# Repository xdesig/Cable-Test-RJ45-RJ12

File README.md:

# Cable Test V0.4

You want a PCB to exercise or learn to solder THT components, here you have one of many.
This provides you with a device to test network cables (RJ45) and telephone cables (RJ12 / 11),
made with normal components, (the most complicated being the LED bar).
You can be complemented with more diodes 1N4148 in anti-parallel soldiers under the LEDS (2, 5..9) to allow to check all cable faults.

Buy PCB in [PCBWAY]

![Top view][DEM]
![Render][PHT]
![Botom view][RENDER]

#B.O.M.
<table cellspacing="0" border="0">
	<colgroup width="38"></colgroup>
	<colgroup width="70"></colgroup>
	<colgroup span="2" width="133"></colgroup>
	<colgroup width="122"></colgroup>
	<colgroup width="85"></colgroup>
	<tr>
		<td height="17" align="left">Qty </td>
		<td align="left">Value</td>
		<td align="left">Device</td>
		<td align="left">Package</td>
		<td align="left">Parts</td>
		<td align="left">Description</td>
	</tr>
	<tr>
		<td height="17" align="left"><br></td>
		<td align="left"><br></td>
		<td align="left"><br></td>
		<td align="left"><br></td>
		<td align="left"><br></td>
		<td align="left"><br></td>
	</tr>
	<tr>
		<td height="17" align="right" sdval="2" sdnum="1110;">2</td>
		<td align="left"><br></td>
		<td align="left"> DS1128-S80BP</td>
		<td align="left">DS1128-S80BP</td>
		<td align="left">J1, J3</td>
		<td align="left">Ethernet Connector</td>
	</tr>
	<tr>
		<td height="17" align="right" sdval="1" sdnum="1110;">1</td>
		<td align="left"><br></td>
		<td align="left"> BATTERY9V</td>
		<td align="left">BATTCON_9V</td>
		<td align="left">BAT1</td>
		<td align="left">Battery Holders</td>
	</tr>
	<tr>
		<td height="17" align="right" sdval="1" sdnum="1110;">2</td>
		<td align="left">100nF</td>
		<td align="left"> C2.5/2</td>
		<td align="left">C2.5-2</td>
		<td align="left">C2, C3</td>
		<td align="left">CAPACITOR</td>
	</tr>
	<tr>
		<td height="17" align="right" sdval="2" sdnum="1110;">2</td>
		<td align="left">10K</td>
		<td align="left"> 1/4 Watt</td>
		<td align="left">0204/7</td>
		<td align="left">R1, R3</td>
		<td align="left">RESISTOR</td>
	</tr>
	<tr>
		<td height="17" align="right" sdval="1" sdnum="1110;">1</td>
		<td align="left">10uF/16V</td>
		<td align="left">2.5mm&ndash;6mm</td>
		<td align="left">E2,5-6</td>
		<td align="left">C1</td>
		<td align="left">POLARIZED CAPACITOR</td>
	</tr>
	<tr>
		<td height="17" align="right" sdval="1" sdnum="1110;">1</td>
		<td align="left">1K</td>
		<td align="left"> R-EU_0204/7</td>
		<td align="left">0204/7</td>
		<td align="left">R4</td>
		<td align="left">RESISTOR</td>
	</tr>
	<tr>
		<td height="17" align="right" sdval="1" sdnum="1110;">8</td>
		<td align="left">1N4148</td>
		<td align="left"> DIODE-D-2.5</td>
		<td align="left">D-2.5</td>
		<td align="left">D1...D8</td>
		<td align="left">DIODE</td>
	</tr>
	<tr>
		<td height="17" align="right" sdval="1" sdnum="1110;">1</td>
		<td align="left">4017N</td>
		<td align="left"> 4017N</td>
		<td align="left">DIL16</td>
		<td align="left">IC2</td>
		<td align="left">COUNTER/DIVIDER</td>
	</tr>
	<tr>
		<td height="17" align="right" sdval="1" sdnum="1110;">1</td>
		<td align="left">47K</td>
		<td align="left"> TRIM_EU-CA6V</td>
		<td align="left">CA6V</td>
		<td align="left">R2</td>
		<td align="left">POTENTIOMETER</td>
	</tr>
	<tr>
		<td height="17" align="right" sdval="1" sdnum="1110;">1</td>
		<td align="left">NE555</td>
		<td align="left"> ICM555</td>
		<td align="left">DIL08</td>
		<td align="left">IC1</td>
		<td align="left">TIMER</td>
	</tr>
	<tr>
		<td height="17" align="right" sdval="1" sdnum="1110;">2</td>
		<td align="left">LB10</td>
		<td align="left"> LB10</td>
		<td align="left">LB10</td>
		<td align="left">LB1,LB2</td>
		<td align="left">10 LED BLOCK</td>
	</tr>
	<tr>
		<td height="17" align="right" sdval="1" sdnum="1110;">1</td>
		<td align="left">SW</td>
		<td align="left"> PB7-0</td>
		<td align="left">PB07_0</td>
		<td align="left">SW1</td>
		<td align="left">8x8mm   DPDT Self-locking Switch</td>
	</tr>
	<tr>
		<td height="17" align="right" sdval="2" sdnum="1110;">2</td>
		<td align="left">RJ11</td>
		<td align="left"> RJ11-6PTH</td>
		<td align="left">95001-6P6C</td>
		<td align="left">J2, J4</td>
		<td align="left">RJ12 Socket 95001-6P6C Female</td>
	</tr>
</table>

## Author and license
* Author: [XDeSIG][TWI01]
* License: CERN-OHL-W V2 [CERN-OHL] and Attribution-ShareAlike 4.0 International [CCBY-SA4.0]

<!-- links -->

[CERN-OHL]: https://ohwr.org/cernohl
[CCBY-SA4.0]: http://creativecommons.org/licenses/by-sa/4.0/
[TWI01]: https://twitter.com/xdesig
[DEM]: Cable-Test-RJ45-RJ12_DEM.png
[PHT]: Cable-Test-RJ45-RJ12_MASTER.png
[RENDER]: Cable-Test-RJ45-RJ12_REMOTE.png

[PCBWAY]: https://www.pcbway.com/project/shareproject/Cable_Test_RJ45___RJ12.html

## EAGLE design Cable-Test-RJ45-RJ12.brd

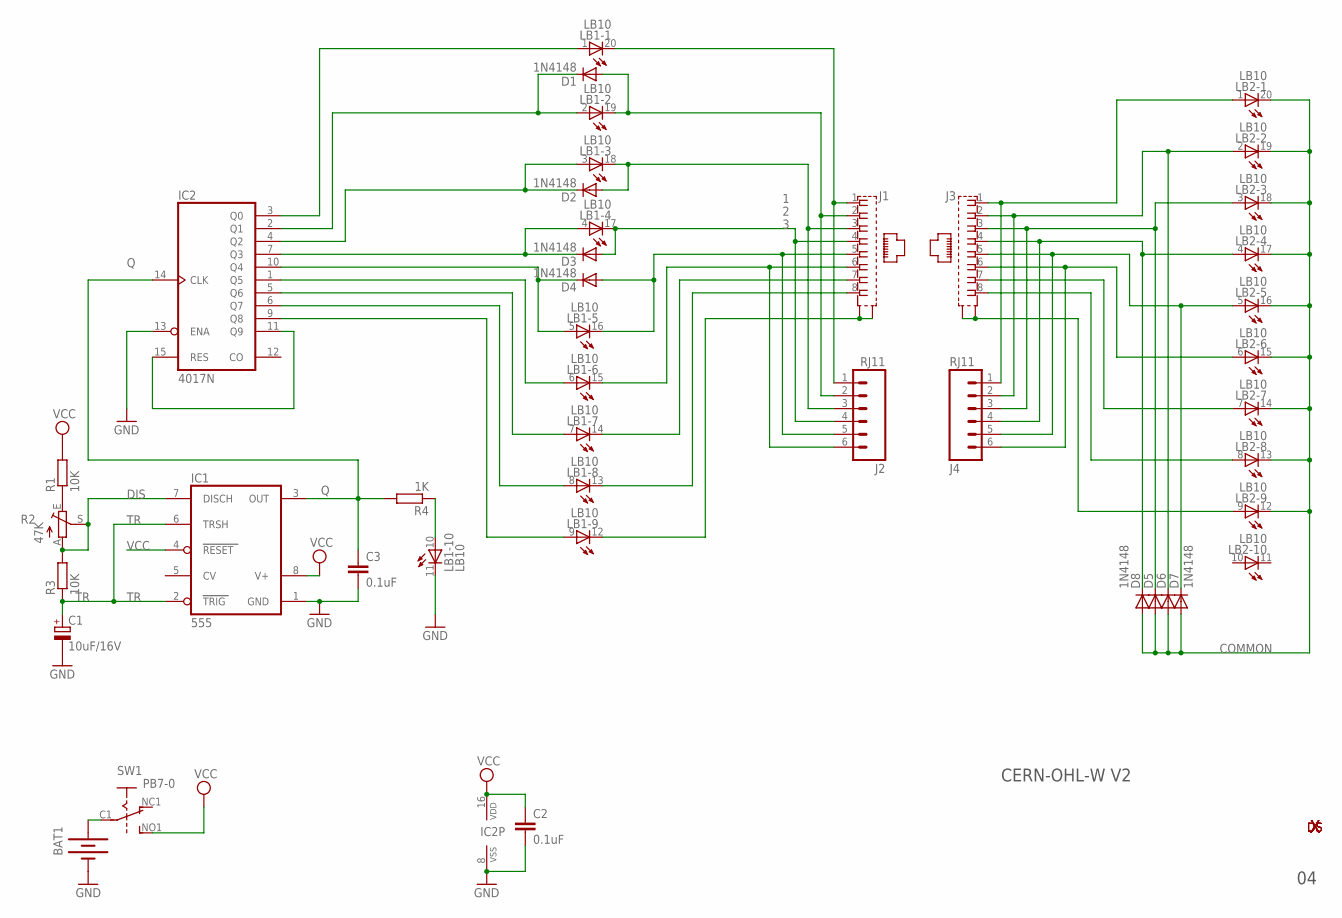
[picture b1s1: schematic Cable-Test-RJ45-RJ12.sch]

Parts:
$1_23_$: XDESIG21; XDESIG
BAT1: BATTERY9V; BATTCON_9V
C1: 10uF/16V; E2,5-6
C2, C3: 0.1uF; C2.5-2
D1, D2, D3, D4, D6, D7: 1N4148; D-2.5
D5, D8: DIODE-D-2.5; D-2.5
IC1: 555; DIL08
IC2: 4017N; DIL16
J1, J3: 555153-1
J2, J4: RJ11; RJ11-6
LB1, LB2: LB10
R1, R3: 10K; 0204/7
R2: 47K; CA6V
R4: 1K; 0204/7
SW1: PB7-0; PB07_0
U$6: XDESIG5MM; XDESIG_CU

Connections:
1: J1.1, J2.1, LB1.20 (C)
2: D1.A, J1.2, J2.2, LB1.19 (C)
3: D2.A, J1.3, J2.3, LB1.18 (C)
4: D3.A, J1.4, J2.4, LB1.17 (C)
COMMON: D5.A, D6.A, D7.A, D8.A, LB2.12 (C), LB2.13 (C), LB2.14 (C), LB2.15 (C), LB2.16 (C), LB2.17 (C), LB2.18 (C), LB2.19 (C), LB2.20 (C)
DIS: IC1.7 (DISCH), R2.A, R2.S, R3.2
G: J1.G1 (S1), J1.G2 (S2), LB1.12 (C)
GND: BAT1.-, C1.-, C2.2, C3.2, IC1.1 (GND), IC2.8 (VSS), IC2.13 (ENA), LB1.11 (C)
unnamed: IC2.11 (Q9), IC2.15 (RES)
unnamed: D6.C, J3.2, J4.2, LB2.2 (A)
unnamed: D2.C, IC2.4 (Q2), LB1.3 (A)
unnamed: D5.C, J3.3, J4.3, LB2.3 (A)
unnamed: IC2.3 (Q0), LB1.1 (A)
unnamed: D8.C, J3.4, J4.4, LB2.4 (A)
unnamed: D7.C, J3.5, J4.5, LB2.5 (A)
unnamed: D4.A, J1.5, J2.5, LB1.16 (C)
unnamed: IC2.9 (Q8), LB1.9 (A)
unnamed: J1.6, J2.6, LB1.15 (C)
unnamed: J3.6, J4.6, LB2.6 (A)
unnamed: D1.C, IC2.2 (Q1), LB1.2 (A)
unnamed: J3.7, LB2.7 (A)
unnamed: J3.8, LB2.8 (A)
unnamed: J3.G1 (S1), J3.G2 (S2), LB2.9 (A)
unnamed: D3.C, IC2.7 (Q3), LB1.4 (A)
unnamed: J3.1, J4.1, LB2.1 (A)
unnamed: R1.1, R2.E
unnamed: BAT1.+, SW1.C1
unnamed: D4.C, IC2.10 (Q4), LB1.5 (A)
unnamed: J1.7, LB1.14 (C)
unnamed: J1.8, LB1.13 (C)
unnamed: IC2.1 (Q5), LB1.6 (A)
unnamed: IC2.5 (Q6), LB1.7 (A)
unnamed: IC2.6 (Q7), LB1.8 (A)
unnamed: LB1.10 (A), R4.1
Q: C3.1, IC1.3 (OUT), IC2.14 (CLK), R4.2
TR: C1.+, IC1.2 (TRIG), IC1.6 (TRSH), R3.1
VCC: C2.1, IC1.4 (RESET), IC1.8 (V+), IC2.16 (VDD), R1.2, SW1.NO1 (S)

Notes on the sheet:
CERN-OHL-W V2

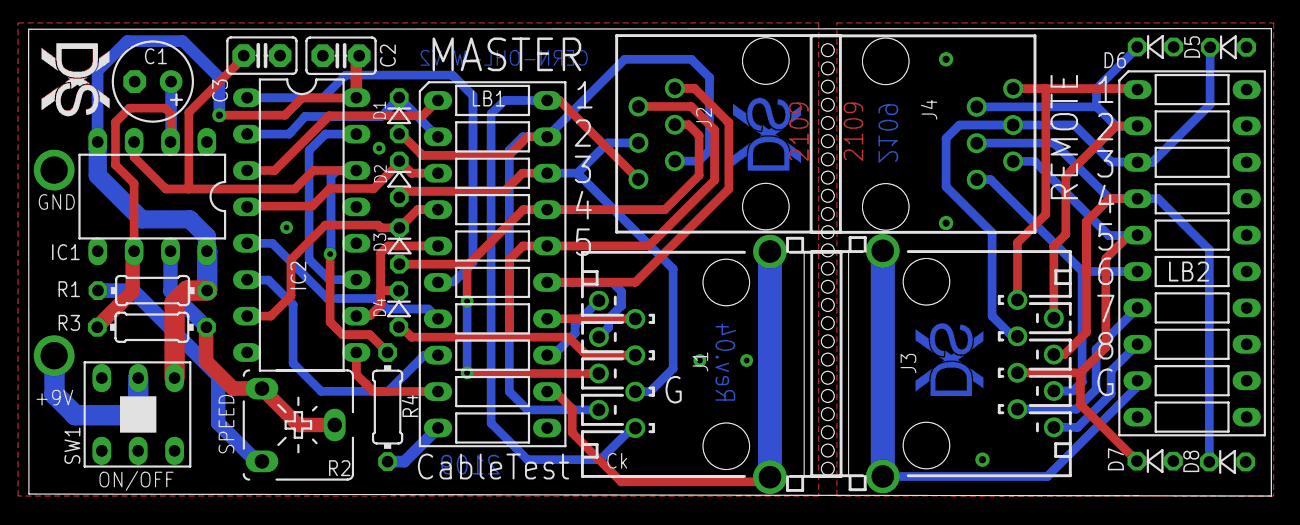
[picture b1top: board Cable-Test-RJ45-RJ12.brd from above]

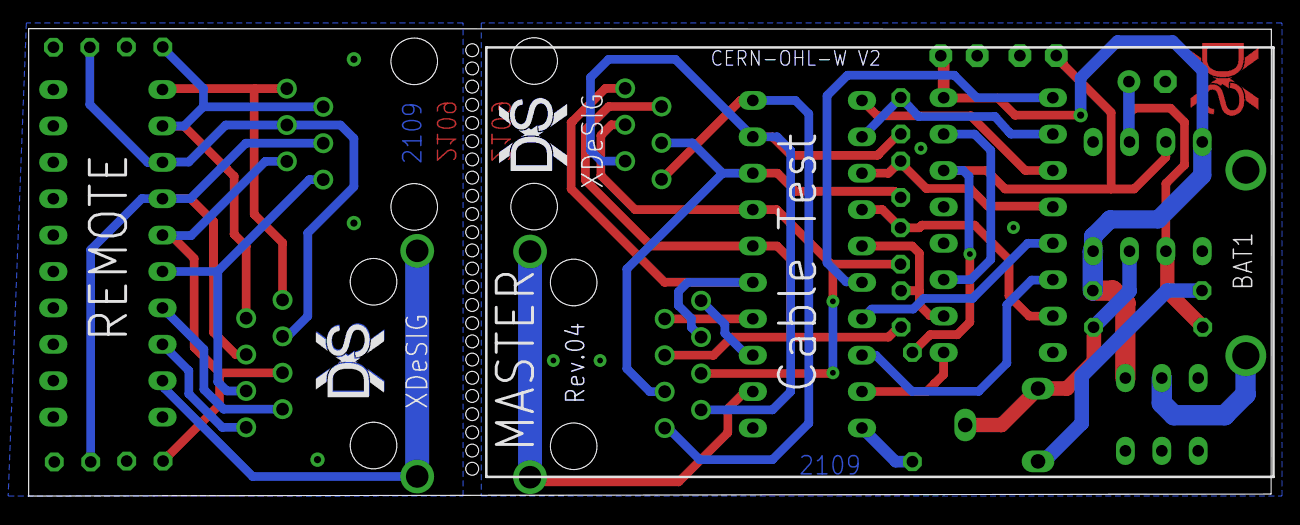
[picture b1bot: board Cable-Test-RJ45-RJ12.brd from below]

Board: 2 copper layers, 86.7 x 32.6 mm, 31 parts (5 on the bottom side), 37 nets.

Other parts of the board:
U$1, U$2: XDESIG5MM; XDESIG_CU
U$3, U$5: XDESIG21; XDESIG

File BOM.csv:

B.O.M.					
Qty 	Value	Device	Package	Parts	Description
					
2		 DS1128-S80BP	DS1128-S80BP	J1, J3	Ethernet Connector
1		 BATTERY9V	BATTCON_9V	BAT1	Battery Holders
1	100nF	 C2.5/2	C2.5-2	C2	CAPACITOR
2	10K	 1/4 Watt	0204/7	R1, R3	RESISTOR
1	10uF/16V	2.5mm6mm	E2,5-6	C1	POLARIZED CAPACITOR
1	1K	 R-EU_0204/7	0204/7	R4	RESISTOR
6	1N4148	 DIODE-D-2.5	D-2.5	D1...D6	DIODE
1	4017N	 4017N	DIL16	IC2	COUNTER/DIVIDER
1	47K	 TRIM_EU-CA6V	CA6V	R2	POTENTIOMETER
1	NE555	 ICM555	DIL08	IC1	TIMER
2	LB10	 LB10	LB10	LB1,LB2	10 LED BLOCK
1	SW	 PB7-0	PB07_0	SW1	8x8mm   DPDT Self-locking Switch
2	RJ11	 RJ11-6PTH	95001-6P6C	J2, J4	RJ12 Socket 95001-6P6C Female

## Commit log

2019-05-10 Initial
2021-03-02 Version 0.4
    Version 0.4, I add a "C3" to stabilize the clock signal impulses
2021-03-02 Version 0.4
2021-03-15 Update V4

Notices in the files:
parts and their libraries:
SparkFun-Electromechanical: Licensing: Creative Commons ShareAlike 4.0 International - https://creativecommons.org/licenses/by-sa/4.0
